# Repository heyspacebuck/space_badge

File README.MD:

# Space Buck's Space Badge

## Thoughts on designing a con badge with boopability

You probably don't need to be told that con badges are useful. Meeting someone in-person when you've only ever seen their avatar and username can be disorienting! This is especially true for real-life events in the furry fandom. A good fur con badge isn't just a nametag, it also shows off some facet of the wearer's personality. "Oh I know that panther, they're good at metalworking," "Oh I know that bear, she cards her own yarn," "Hey it's Space Buck, he makes goofy electronics!"

Naturally I thought it would be fun to make a PCB con badge for myself. The obverse face has, well, my face, and three large copper pours for capacitive touch purposes. The reverse has twelve WS2812B addressable LEDs, an ATtiny85, and a trio of dead-simple AT42QT1011 capacitive touch sensors. It's powered by a pair of 10440 li-ion cells and a 5V LDO, simply because I have a ton of those lying around. The ATtiny85 is programmed in-circuit with a SOICbite connector. In theory I could have just used the SOIC clip as intended, but for whatever reason I can never get them to make secure connections that way.

How it works: The copper pours under the nose and the antlers are the only inputs and the RGB LEDs are the only outputs. Booping the snoot turns the system on or off. When on, one of six FastLED patterns plays across the LEDs. To switch to the next/previous patterns, just touch the right/left antlers.

The cute art is by [Fenn, @rainandmaple on Twitter](https://twitter.com/rainandmaple)! I got white soldermask because I intend to paint it someday. The git repo contains the circuit I used, but not Fenn's artwork. I don't recommend using the same circuit I used! Which brings us to future hardware improvements....

## Future hardware improvements

I'm happy with the badge for myself, but if I were making one for someone else, I'd put a lot more care into it. A physical power switch, for sure. A more normal Li-Po pouch battery, and a built-in USB charge circuit (sorry not sorry, I'm still using USB Micro B ports on all my designs). More LED patterns. I've designed a proof-of-concept circuit but haven't tried it for real yet.

### Power consumption

It should be easy to set up deep-sleep mode on the ATtiny85 and wait for an interrupt to turn the LEDs on. I suppose it's still possible to update this version to do that; I'd just have to update the code. In fact, I think I will do that!

...

Okay I'm back, the badge now enters deep-sleep mode when the lights are off and turns back on with a pin change interrupt. Now I know to attach this specific touch sensor to the INT0 pin (PB0, pin 5) for an easier time detecting rising-edge interrupts only.

### Power supply

The first badge's power system is bad: two 10440 li-ion cells in series, dropped to 5V with an LDO. I only did this because those were the parts I had on-hand. Were I building this for someone else, I'd use a regular pouch li-po cell, something in the 350-500 mAh range, and a boost converter like the TPS613222A to get the 5 volts expected by the WS2812b LEDs. And, of course, a built-in recharging circuit. I'd also add a physical power switch. We don't want the cap-touch sensors turning the badge on at inopportune times.

### Programming

Goodbye, SOICbite. The next version of the badge will have *no* visible copper on the obverse face. The SOICbite is lovely but as long as I'm using a SOIC-8 microcontroller I should just use the SOIC clip as intended. That said, I have trouble with keeping my SOIC clip to secured on the IC, and I like offering large pads for soldering wires to, so I've also stuck on some SMD pads that can be soldered to or probed with pogo pins.

The light show patterns are demos from the FastLED Arduino library. When compiled the current sketch uses about 70% of the ATtiny85's 8k flash, and about 40% of the RAM, so there's plenty of room for new features.

### Part flexibility

Ah, the chip shortage. Judging by the AT42QT101x lead times, I won't be using that IC in any designs for a while. The TTP223, which is a similar and much cheaper chip, is still available from many places, so I can adjust my designs to use that without much fuss. Alternately, I'd like to try turning some ATtiny10's into cap-touch sensors! The datasheet promises that Atmel's QTouch capacitive touch library is supported, but the actual documentation and libraries are nearly impossible to find on their website. Someone from Microchip guided me through the maze of broken links to get to some inscrutable libraries and an ATtiny10-specific tool that I'd describe as "so Visual Basic it hurts". It will take some time (and I'll have to find my HV programmer) but that's something to look forward to.

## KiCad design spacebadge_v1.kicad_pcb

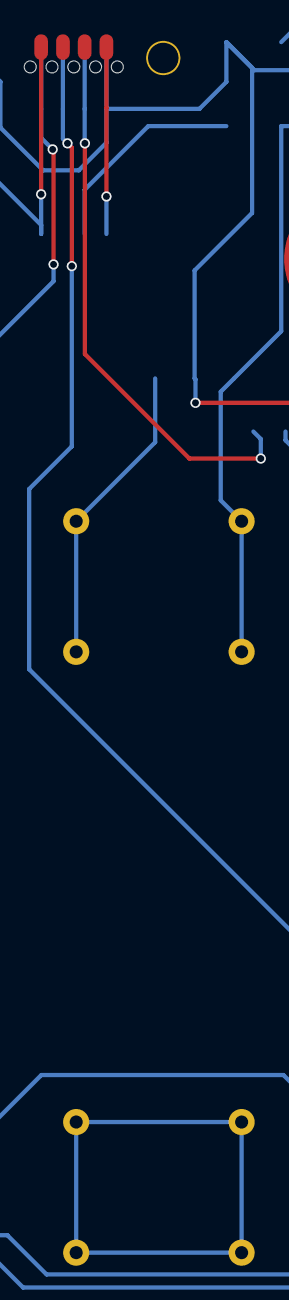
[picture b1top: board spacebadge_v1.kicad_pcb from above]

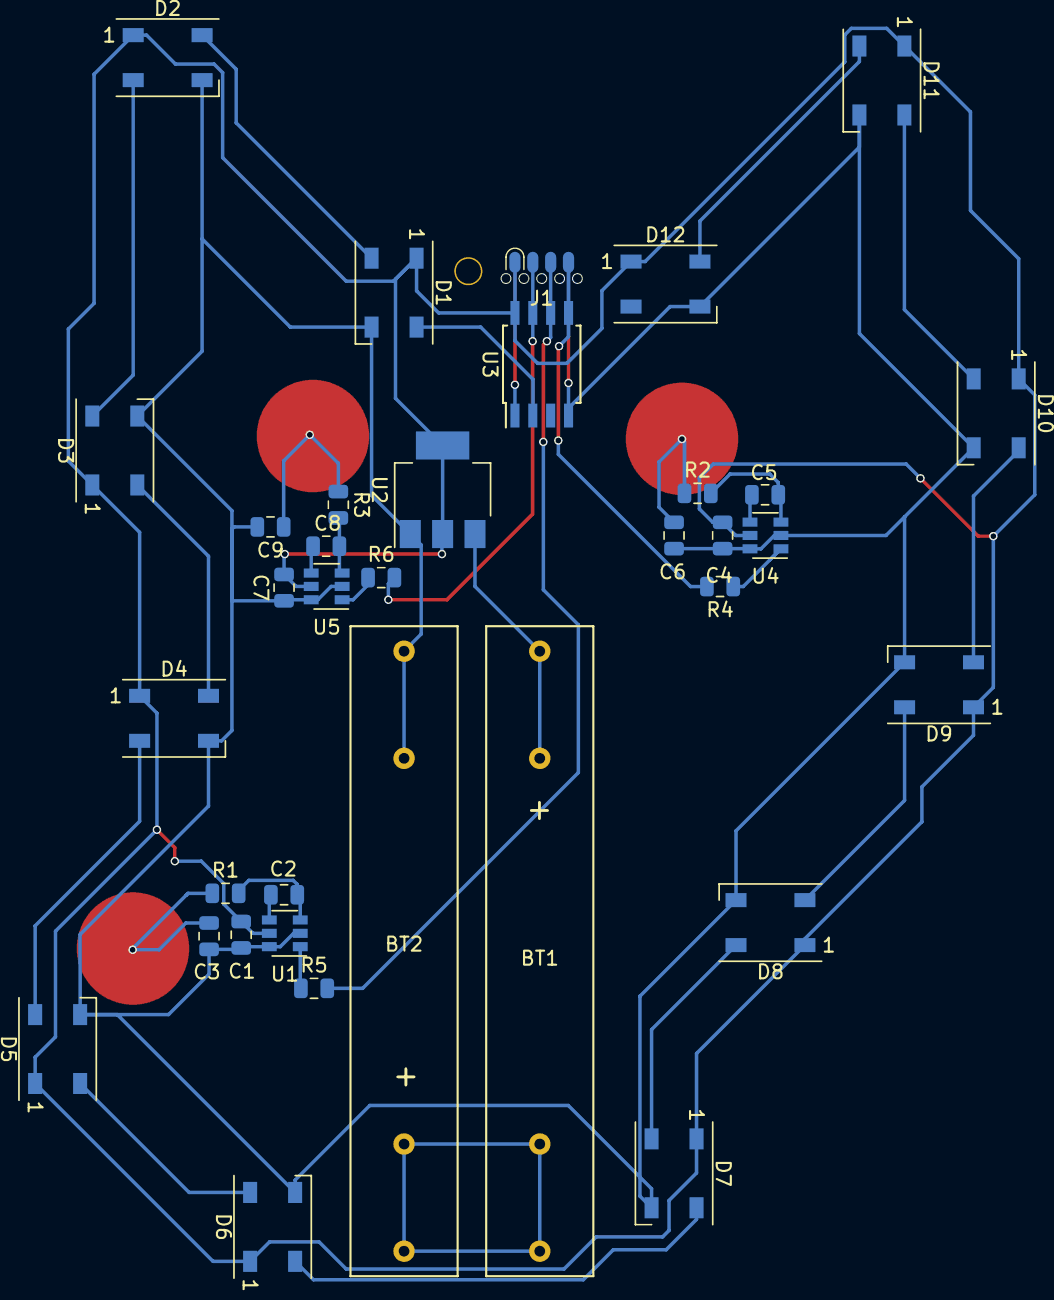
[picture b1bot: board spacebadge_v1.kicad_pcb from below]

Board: 2 copper layers, 35 parts (35 on the bottom side), 32 nets.

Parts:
BT1, BT2: Battery_Cell; bk-82-10440
C1, C4, C7: .1 μF; C_0805_2012Metric
C2, C5, C8: .01 μF; C_0805_2012Metric
C3, C6, C9: 5-20 pF; C_0805_2012Metric
D1, D2, D3, D4, D5, D6, D7, D8, D9, D10, D11, D12: WS2812B; LED_WS2812B_PLCC4_5.0x5.0mm_P3.2mm
J1: Conn_02x04_Counter_Clockwise; SOIC_clipProgSmall
R1, R2, R3, R4, R5, R6: 1 kΩ; R_0805_2012Metric
U1, U4, U5: AT42QT1011-TSHR; SOT-23-6
U2: AP1117-50; SOT-223-3_TabPin2
U3: ATtiny85-20SU; SOIJ-8_5.3x5.3mm_P1.27mm

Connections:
0V: BT2.2, C1.1, C3.2, C4.1, C6.2, C7.1, C9.2, D1.3, D2.3, D3.3, D4.3, D5.3, D6.3, D7.3, D8.3, D9.3, D10.3, D11.3, D12.3, J1.5, U1.2, U1.6, U2.1, U3.4, U4.2, U4.6, U5.2, U5.6
5V: C1.2, C4.2, C7.2, D1.1, D2.1, D3.1, D4.1, D5.1, D6.1, D7.1, D8.1, D9.1, D10.1, D11.1, D12.1, J1.1, U1.5, U2.2, U3.8, U4.5, U5.5
/clk: J1.2, R6.2, U3.7
/sdi: J1.4, R4.2, U3.5
/sdo: J1.3, R5.2, U3.6
/~cs: J1.8, U3.1
unnamed: BT1.1, U2.3
unnamed: BT1.2, BT2.1
unnamed: C2.1, R1.2, U1.3
unnamed: C2.2, U1.4
unnamed: C5.1, R2.2, U4.3
unnamed: C5.2, U4.4
unnamed: C8.1, R3.2, U5.3
unnamed: C8.2, U5.4
unnamed: D1.2, D2.4
unnamed: D2.2, D3.4
unnamed: D3.2, D4.4
unnamed: D4.2, D5.4
unnamed: D5.2, D6.4
unnamed: D6.2, D7.4
unnamed: D7.2, D8.4
unnamed: D8.2, D9.4
unnamed: D10.2, D11.4
unnamed: D9.2, D10.4
unnamed: D11.2, D12.4
l_antler: C6.1, R2.1
led: D1.4, U3.2
r_antler: C9.1, R3.1
snout: C3.1, R1.1
touch0: R5.1, U1.1
touch1: R4.1, U4.1
touch2: R6.1, U5.1

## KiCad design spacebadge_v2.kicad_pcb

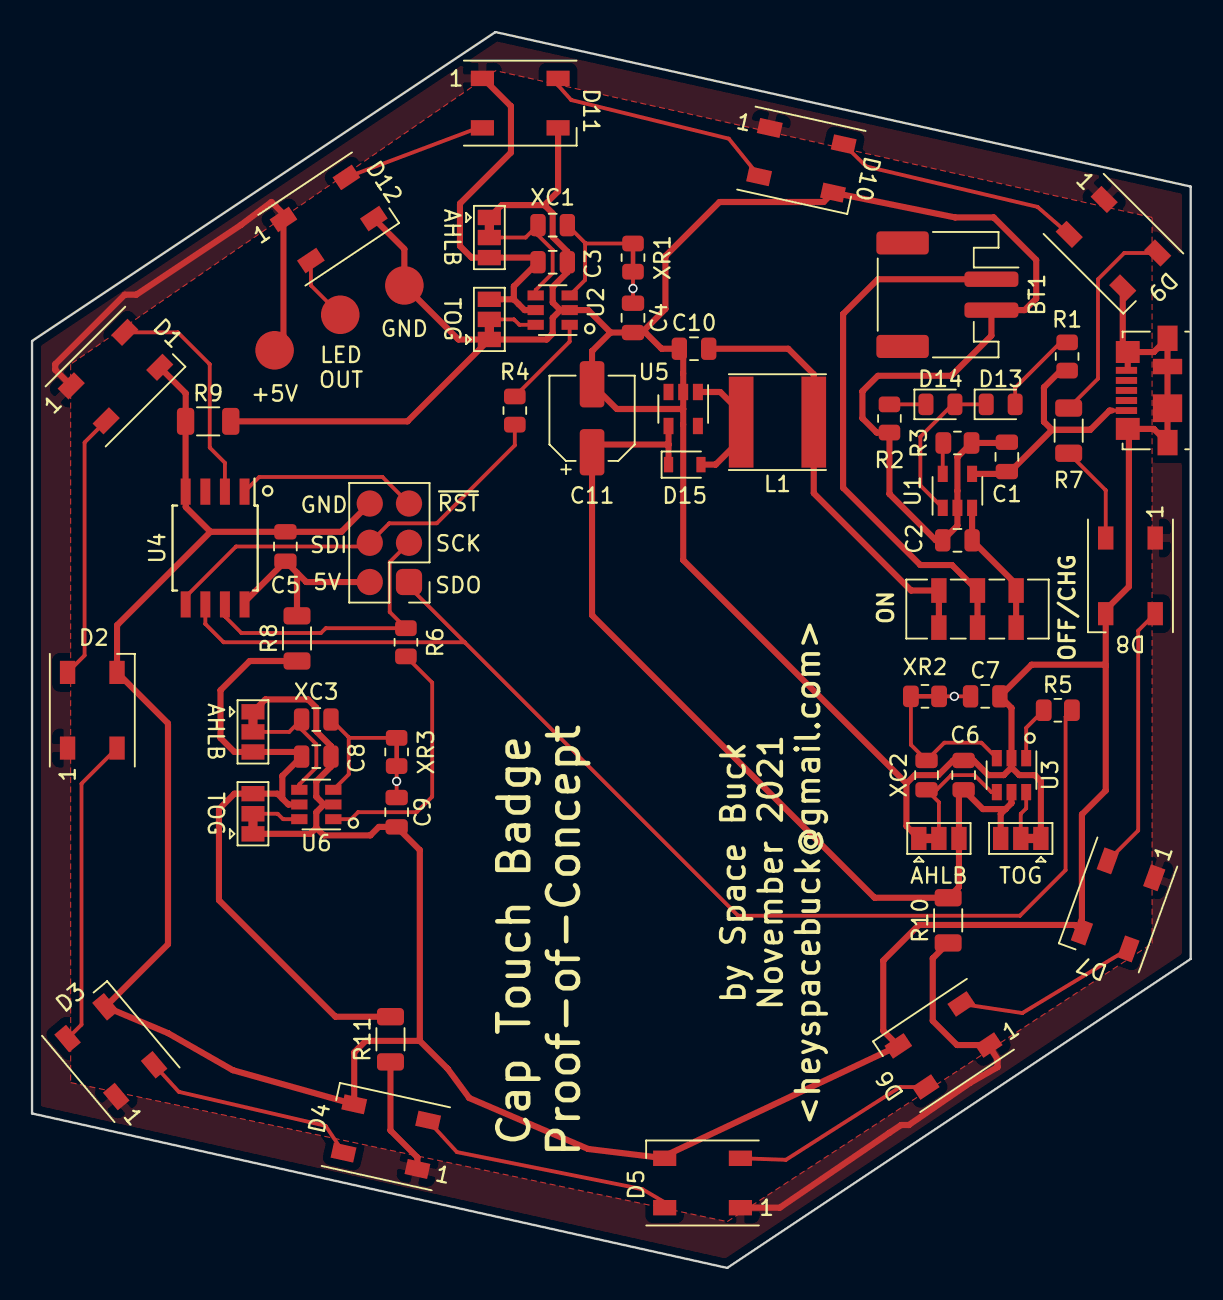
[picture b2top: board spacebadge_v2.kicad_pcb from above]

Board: 2 copper layers, 75.0 x 80.0 mm, 63 parts (0 on the bottom side), 46 nets.

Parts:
BT1: JST-PH 2 pin; JST_PH_S2B-PH-SM4-TB_1x02-1MP_P2.00mm_Horizontal
C1, C2: 10μF; C_0805_2012Metric
C3, C5, C6, C8: 0.1μF; C_0805_2012Metric
C4, C7, C9: 10pF; C_0805_2012Metric
C10: 4.7μF; C_0805_2012Metric
C11: 22μF; CP_Elec_5x5.4
D1, D2, D3, D4, D5, D6, D7, D8, D9, D10, D11, D12: WS2812B; LED_WS2812B_PLCC4_5.0x5.0mm_P3.2mm
D13: Red; LED_0805_2012Metric
D14: Green; LED_0805_2012Metric
D15: Schottky; D_SOD-323
J1: Conn_02x03_Odd_Even; SMDPads_2x03_P2.54mm
J2: USB_B_Micro; USB_Micro-B_Molex_47346-0001
JP1, JP2, JP3, JP4, JP5, JP6: Jumper_3_Bridged12_Small; SolderJumper-3_P1.3mm_Bridged12_Pad1.0x1.5mm
L1: 2.2μH; L_Taiyo-Yuden_NR-60xx
R1, R2: 2kΩ; R_0805_2012Metric
R3: R; R_0805_2012Metric
R4, R5, R6: 1kΩ; R_0805_2012Metric
R7, R8, R9, R10, R11: 0Ω; R_1206_3216Metric
SW1: SW_SPDT; SW_DPDT_CK_JS202011JCQN
TP1, TP2, TP3: TestPoint; TestPoint_Pad_D2.5mm
U1: MCP73831-2-OT; SOT-23-5
U2, U3, U6: TTP223-BA6; SOT-23-6
U4: ATtiny85-20SU; SOIJ-8_5.3x5.3mm_P1.27mm
U5: TPS613222ADBV; SOT-23-5
XC1, XC2, XC3: Jumper_NO_Small; C_0805_2012Metric
XR1, XR2, XR3: Jumper_NC_Small; 0805_NC

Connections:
0V: BT1.2, C1.1, C2.1, C3.1, C4.2, C5.1, C6.1, C7.2, C8.1, C9.2, C10.1, C11.2, D1.3, D2.3, D3.3, D4.3, D5.3, D6.3, D7.3, D8.3, D9.3, D10.3, D11.3, D12.3, J1.6, J2.5, J2.6, JP1.1, JP2.1, JP3.1, JP4.1, JP5.1, JP6.1, R2.1, R3.2, R9.1, R9.2, TP3.1, U1.2, U2.2, U3.2, U4.4, U5.2, U6.2
5V: C3.2, C6.2, C11.1, D1.1, D2.1, D3.1, D4.1, D5.1, D6.1, D7.1, D8.1, D9.1, D10.1, D11.1, D12.1, D15.1, JP1.3, JP2.3, JP3.3, JP4.3, R10.1, R10.2, R11.1, TP1.1, U2.5, U3.5, U5.4
/5v_a: C5.2, J1.2, R8.2, U4.8
/5v_c: C8.2, JP5.3, JP6.3, R8.1, R11.2, U6.5
/clk: J1.3, R6.2, U4.7
/pad0: C4.1, XR1.1
/pad1: C7.1, XR2.1
/pad2: C9.1, XR3.1
/sdi: J1.4, R4.2, U4.5
/sdo: J1.1, R5.2, U4.6
/~cs: J1.5, U4.1
BATT: BT1.1, SW1.2
LED_control: D1.4, U4.2
unnamed: C1.2, J2.1, R1.1, U1.4
unnamed: C10.2, L1.1, SW1.3
unnamed: D1.2, D2.4
unnamed: D2.2, D3.4
unnamed: D3.2, D4.4
unnamed: D4.2, D5.4
unnamed: D5.2, D6.4
unnamed: D6.2, D7.4
unnamed: D7.2, D8.4
unnamed: D8.2, R7.2
unnamed: D9.4, R7.1
unnamed: D10.2, D11.4
unnamed: D9.2, D10.4
unnamed: D11.2, D12.4
unnamed: D12.2, TP2.1
unnamed: D13.1, D14.2, U1.1
unnamed: D13.2, R1.2
unnamed: D14.1, R2.2
unnamed: D15.2, L1.2, U5.1
unnamed: JP1.2, U2.4, XC1.2
unnamed: JP2.2, U2.6
unnamed: JP3.2, U3.4, XC2.2
unnamed: JP4.2, U3.6
unnamed: JP5.2, U6.4, XC3.2
unnamed: JP6.2, U6.6
unnamed: R3.1, U1.5
unnamed: U2.3, XC1.1, XR1.2
unnamed: U3.3, XC2.1, XR2.2
unnamed: U6.3, XC3.1, XR3.2
charging: C2.2, SW1.1, U1.3
touch0: R4.1, U2.1
touch1: R5.1, U3.1
touch2: R6.1, U6.1

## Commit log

2021-12-09 Initial public commit
2021-12-09 Create LICENSE
2021-12-09 Add schematic v2
